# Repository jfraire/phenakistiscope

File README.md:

# phenakistiscope
An ATtiny85 circuit to build a phénakistiscope

A phénakistiscope is a toy invented in the XIX century, and it is one of the first devices to display animations.

It is usually a disk with the animation frames painted in one face, at regular intervals. It has cut-outs, also spaced regularly. The user would see the disk reflected on a mirror, through the slits. When the disk is spun, the animation comes to life!

It is easy to find beautiful disks from that time. You can find a few in the [Wikipedia page](https://en.wikipedia.org/wiki/Phenakistiscope). If you are interested, be sure to take a look at [The wheel of life](http://www.stephenherbert.co.uk/wheelHOME.htm). It is a site full of historic information and it contains some of the most beautiful disks I've seen.

## This project

Another way of animating these disks is with a physical device. In these times, a small, rotating servo-motor and some LEDs that turn on and off will work. To synchronize the the motor with the LEDs, this project uses a couple of potentiometers. This is nice: You end up playing with the knobs to get your animation just right.

In this repository you will find the electronic schema, the code, the BOM, and the KiCAD file.

Also, note that the terms *zoetrope* and *phénakistiscope* refer to two different devices. However, zoetropes may include the same kind of disks at the bottom of the animation drums and they exploit the same principle to display animations. The KiCAD files are named *zoetrope*.

## Bill of materials

Item | Reference | Description
---|---|---
U1|LM7805|5V voltage regulator
U2|ATTINY85-20PU|ATtiny85 micro-controller
R1|220 Ω|Resistor
C1|0.33 μF|Capacitor
C2|0.1 μF|Capacitor
C3|0.1 μF|Capacitor
J1|Screw Terminal 01x02|Terminal block for power 
J2|Conn 01x03 Male|3 pins, male connector for the servo motor
J3|Screw Terminal 01x06|Terminal block for the potentiometers
J4|Screw Terminal 01x02|Terminal block for the LEDs

And not in the schema:

1. Continuous rotation servo motor FS90R
2. Two 10kΩ potentiometers
3. Four white LEDs

## Contents of the repository

You will find the KiCAD files under `kicad`. The code and make file for the micro-controller is in `src`. The KiCAD files include the lay out of the PCB, which is small and easy to solder. The `img` folder contains an example disk.

## Credits

The makefile to compile this project was taken from the book [Make: AVR Programming](https://www.amazon.fr/Make-AVR-Programming-Elliot-Williams/dp/1449355781), by Elliot Williams. This book has given me more than a few hours of pleasure.

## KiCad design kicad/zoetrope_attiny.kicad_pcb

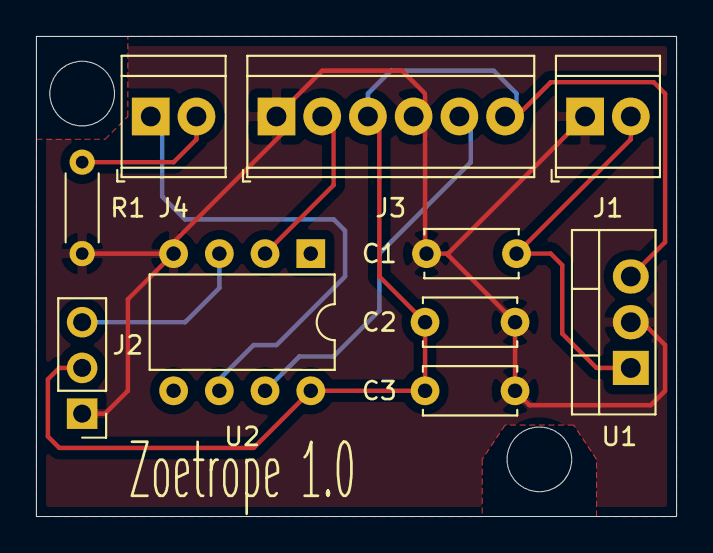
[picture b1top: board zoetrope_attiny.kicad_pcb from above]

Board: 2 copper layers, 35.6 x 26.7 mm, 10 parts (0 on the bottom side), 8 nets.

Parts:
C1: 0.33 μF; C_Disc_D5.0mm_W2.5mm_P5.00mm
C2, C3: 0.1 μF; C_Disc_D5.0mm_W2.5mm_P5.00mm
J1, J4: Screw_Terminal_01x02; TerminalBlock_TE_282834-2_1x02_P2.54mm_Horizontal
J2: Conn_01x03_Male; PinHeader_1x03_P2.54mm_Vertical
J3: Screw_Terminal_01x06; TerminalBlock_TE_282834-6_1x06_P2.54mm_Horizontal
R1: 220 Ω; R_Axial_DIN0204_L3.6mm_D1.6mm_P5.08mm_Horizontal
U1: LM7805_TO220; TO-220-3_Vertical
U2: ATTINY85-20PU; DIP-8_W7.62mm

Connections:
+5V: C2.1, C3.1, J2.2, J3.3, J3.6, U1.3, U2.8
GND: C1.2, C2.2, C3.2, J1.1, J2.1, J3.1, J3.4, R1.2, U1.2, U2.4
LED: J4.1, U2.6
unnamed: C1.1, J1.2, U1.1
unnamed: J4.2, R1.1
POT1: J3.5, U2.7
POT2: J3.2, U2.2
SERVO: J2.3, U2.3

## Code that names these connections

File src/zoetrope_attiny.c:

/* -----------------------------------------------
   Program that controls the period of a PWM
   signal with a potentiometer, while it moves a
   servo motor at a constant speed.
   It uses timer 0, 1, and the ADC
   Works with ATTiny85
   ----------------------------------------------- */
#include <avr/io.h>
#include <avr/interrupt.h>
#include <util/delay.h>

#define LED PB1
#define SERVO PB4
#define POT1 ADC1
#define POT2 ADC3

const uint8_t bright_time = 3;

uint8_t read_adc(uint8_t channel) {
    ADMUX &= (0xF0);                        // Clear the channel selection
    ADMUX |= channel;                       // Read from ADCX
    ADCSRA |= (1 << ADSC);                  // Start conversion
    loop_until_bit_is_clear(ADCSRA, ADSC);
    return ADCH;
}

int main(void) {
    // Set LED and SERVO pins for output
    DDRB = (1 << SERVO) | (1 << LED);

    // Initialize the ADC -- Use VCC as reference
    ADMUX = 0;                              // Clearing REFS0-2 selects VCC as ref
    ADMUX  |= (1 << ADLAR);                 // Use only the most significant 8 bits
    ADCSRA |= (1 << ADPS1) | (1 << ADPS0);  // Set prescaler to 1/8 
    ADCSRA |= (1 << ADEN);                  // Enable ADC

    // Configure timer 0 in fast PWM mode with variable period
    // The period is modified by chaning OCR0A, and the signal turns off on OCR0B
    // So, output is at OC0B, PB1
    TCCR0A = (1 << WGM01) | (1 << WGM00);   // Fast PWM mode reseting at OCR0A
    TCCR0B = (1 << WGM02);                  // (mode 7)
    TCCR0A |= (1 << COM0B1);                // Output non-inverting on OC0B (PB1)
    TCCR0B |= (1 << CS02) | (1 << CS00);    // Set the prescaler to 1/1024
    OCR0B = bright_time;                    // Time to keep the output high

    // Configure timer 1 in PWM mode. Output is PB4 (OC1B) --> SERVO
    // The ON period should last between 900 and 2100 us --> 1200 us
    // And the frequency of the signal should be between 50 and 100 Hz
    // Because it is an 8-bit timer, its period is divided by 256, maximum
    // A prescaler of 64 will give a period of 16.4 ms with a resolution of 64 us
    // The 1200 us can be divided into only 18.75 bins...
    GTCCR = (1 << PWM1B);                    // Enable PWM mode on OCR1A
    GTCCR |= (1 << COM1B1);                  // OC1A turns on at 0, resets at OCR1C
    TCCR1 = (1 << CS12) | (1 << CS11) | (1 << CS10);
    OCR1C = 0xFF;                           // Pulse duration of 256 * 64 us, or 16.38 ms

    // ------ Event loop ------ //
    while (1) {
        // Read the 1st potentiometer and change the period of the PWM
        // signal for the LED in timer 0
        OCR0A = read_adc(1);

        // Read the 2nd potentiometer and change the high duration of the PWM
        // signal for the servo motor in timer 1
        // The 0-255 signal should be mapped to 0-18.75
        // The minimum pulse is 900 us, or 14 clock ticks of 64 us
        uint8_t speed_servo = read_adc(3);
        OCR1B = (uint8_t)(18.75 * speed_servo / 255.0 + 14.06);
    }
    return 0;
}

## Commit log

2021-12-28 Testing an image in README.md
2021-12-28 Added an example disk
2021-12-28 Added the BOM to the README file
2021-12-28 Updated the README file
2021-12-28 Added the cow abduction disk
2022-01-01 Added credit to Make: AVR Programming
